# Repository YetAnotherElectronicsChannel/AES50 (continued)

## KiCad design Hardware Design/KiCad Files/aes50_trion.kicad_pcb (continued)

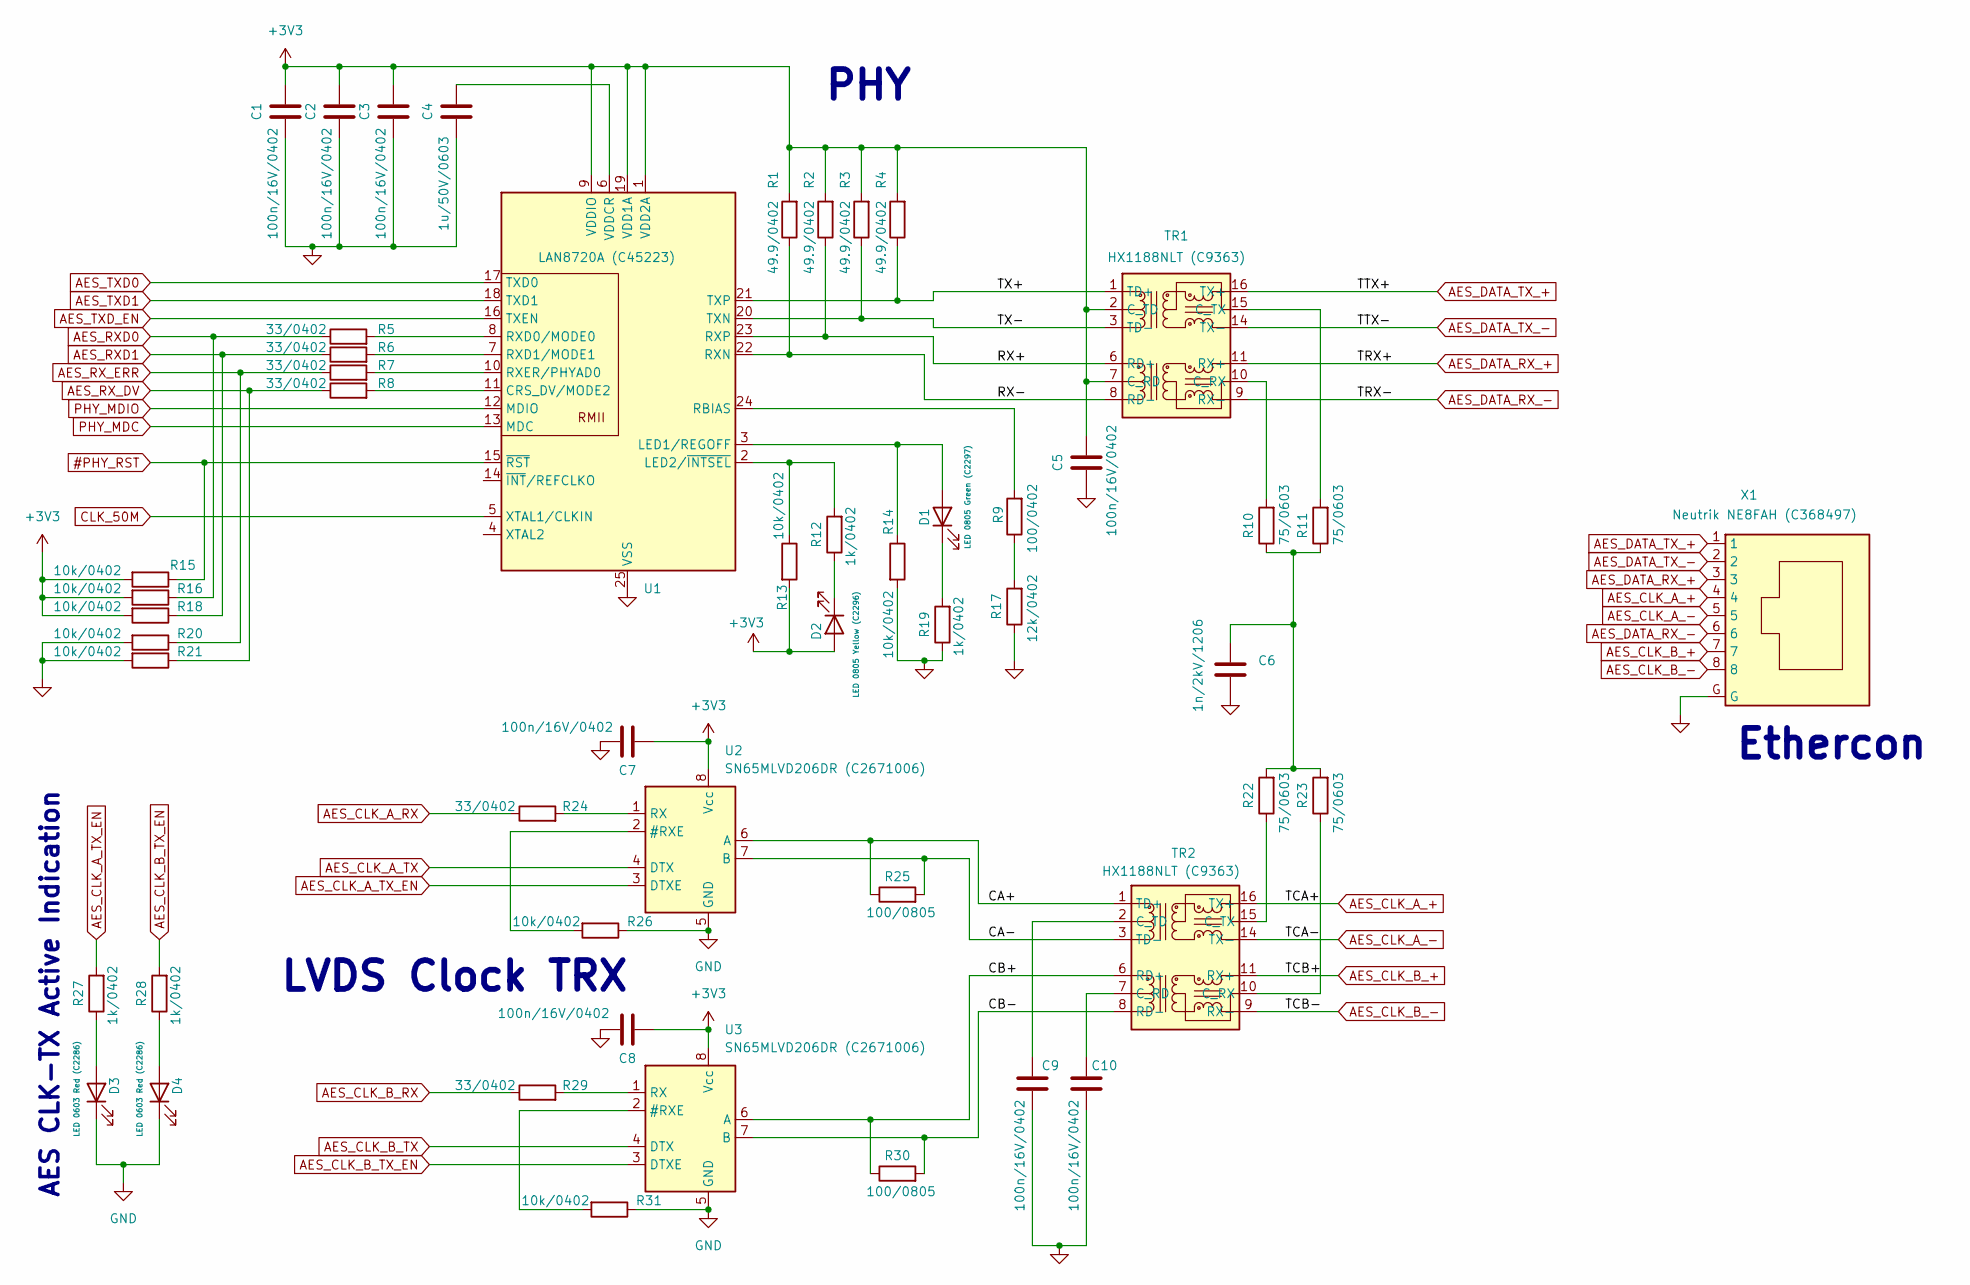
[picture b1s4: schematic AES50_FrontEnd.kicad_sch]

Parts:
C1, C2, C3, C5, C7, C8, C9, C10: 100n/16V/0402; C_0402_1005Metric
C4: 1u/50V/0603; C_0603_1608Metric
C6: 1n/2kV/1206; C_1206_3216Metric
D1: LED 0805 Green (C2297); LED_0805_2012Metric
D2: LED 0805 Yellow (C2296); LED_0805_2012Metric
D3, D4: LED 0603 Red (C2286); LED_0603_1608Metric
R1, R2, R3, R4: 49.9/0402; R_0402_1005Metric
R5, R6, R7, R8, R24, R29: 33/0402; R_0402_1005Metric
R9: 100/0402; R_0402_1005Metric
R10, R11, R22, R23: 75/0603; R_0603_1608Metric
R12, R19, R27, R28: 1k/0402; R_0402_1005Metric
R13, R14, R15, R16, R18, R20, R21, R26, R31: 10k/0402; R_0402_1005Metric
R17: 12k/0402; R_0402_1005Metric
R25, R30: 100/0805; R_0805_2012Metric
TR1, TR2: HX1188NLT (C9363); HX1188NL
U1: LAN8720A (C45223); VQFN-24-1EP_4x4mm_P0.5mm_EP2.5x2.5mm_ThermalVias
U2, U3: SN65MLVD206DR (C2671006); SOIC-8_3.9x4.9mm_P1.27mm
X1: Neutrik NE8FAH (C368497); Neutrik NE8FAH

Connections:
#PHY_RST: R15.1, U1.15 (~RST); also elsewhere on the board
+3V3: C1.2, C2.2, C3.2, C5.2, C7.1, C8.1, D2.2 (A), R1.2, R2.2, R3.2, R4.2, R13.2, R15.2, R16.2, R18.2, TR1.2 (C_TD), TR1.7 (C_RD), U1.1 (VDD2A), U1.9 (VDDIO), U1.19 (VDD1A), U2.8 (Vcc), U3.8 (Vcc); also elsewhere on the board
/AES50_FrontEnd/CA+: R25.1, TR2.1 (TD+), U2.6 (A)
/AES50_FrontEnd/CA-: R25.2, TR2.3 (TD-), U2.7 (B)
/AES50_FrontEnd/CB+: R30.1, TR2.6 (RD+), U3.6 (A)
/AES50_FrontEnd/CB-: R30.2, TR2.8 (RD-), U3.7 (B)
/AES50_FrontEnd/RX+: R2.1, TR1.6 (RD+), U1.23 (RXP)
/AES50_FrontEnd/RX-: R1.1, TR1.8 (RD-), U1.22 (RXN)
/AES50_FrontEnd/TX+: R4.1, TR1.1 (TD+), U1.21 (TXP)
/AES50_FrontEnd/TX-: R3.1, TR1.3 (TD-), U1.20 (TXN)
AES_CLK_A_+: TR2.16 (TX+), X1.4
AES_CLK_A_-: TR2.14 (TX-), X1.5
AES_CLK_A_RX: R24.1; also elsewhere on the board
AES_CLK_A_TX: U2.4 (DTX); also elsewhere on the board
AES_CLK_A_TX_EN: R27.2, U2.3 (DTXE); also elsewhere on the board
AES_CLK_B_+: TR2.11 (RX+), X1.7
AES_CLK_B_-: TR2.9 (RX-), X1.8
AES_CLK_B_RX: R29.1; also elsewhere on the board
AES_CLK_B_TX: U3.4 (DTX); also elsewhere on the board
AES_CLK_B_TX_EN: R28.2, U3.3 (DTXE); also elsewhere on the board
AES_DATA_RX_+: TR1.11 (RX+), X1.3
AES_DATA_RX_-: TR1.9 (RX-), X1.6
AES_DATA_TX_+: TR1.16 (TX+), X1.1
AES_DATA_TX_-: TR1.14 (TX-), X1.2
AES_RXD0: R5.1, R16.1; also elsewhere on the board
AES_RXD1: R6.1, R18.1; also elsewhere on the board
AES_RX_DV: R8.1, R21.1; also elsewhere on the board
AES_RX_ERR: R7.1, R20.1; also elsewhere on the board
AES_TXD0: U1.17 (TXD0); also elsewhere on the board
AES_TXD1: U1.18 (TXD1); also elsewhere on the board
AES_TXD_EN: U1.16 (TXEN); also elsewhere on the board
CLK_50M: U1.5 (XTAL1/CLKIN); also elsewhere on the board
GND: C1.1, C2.1, C3.1, C4.1, C5.1, C6.2, C7.2, C8.2, C9.1, C10.1, D3.1 (K), D4.1 (K), R14.2, R17.1, R19.1, R20.2, R21.2, R26.1, R31.1, U1.25 (VSS), U2.5 (GND), U3.5 (GND), X1.G; also elsewhere on the board
unnamed: C6.1, R10.1, R11.1, R22.2, R23.2
unnamed: D1.2 (A), R14.1, U1.3 (LED1/REGOFF)
unnamed: D1.1 (K), R19.2
unnamed: D2.1 (K), R12.1
unnamed: D3.2 (A), R27.1
unnamed: D4.2 (A), R28.1
unnamed: R9.1, R17.2
unnamed: R10.2, TR1.10 (C_RX)
unnamed: R11.2, TR1.15 (C_TX)
unnamed: C10.2, TR2.7 (C_RD)
unnamed: R23.1, TR2.10 (C_RX)
unnamed: C9.2, TR2.2 (C_TD)
unnamed: R22.1, TR2.15 (C_TX)
unnamed: R8.2, U1.11 (CRS_DV/MODE2)
unnamed: R12.2, R13.1, U1.2 (LED2/~INTSEL)
unnamed: R9.2, U1.24 (RBIAS)
unnamed: R5.2, U1.8 (RXD0/MODE0)
unnamed: R6.2, U1.7 (RXD1/MODE1)
unnamed: R7.2, U1.10 (RXER/PHYAD0)
unnamed: C4.2, U1.6 (VDDCR)
unnamed: R26.2, U2.2 (#RXE)
unnamed: R24.2, U2.1 (RX)
unnamed: R31.2, U3.2 (#RXE)
unnamed: R29.2, U3.1 (RX)
PHY_MDC: U1.13 (MDC); also elsewhere on the board
PHY_MDIO: U1.12 (MDIO); also elsewhere on the board

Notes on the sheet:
AES CLK-TX Active Indication
LVDS Clock TRX
PHY
Ethercon

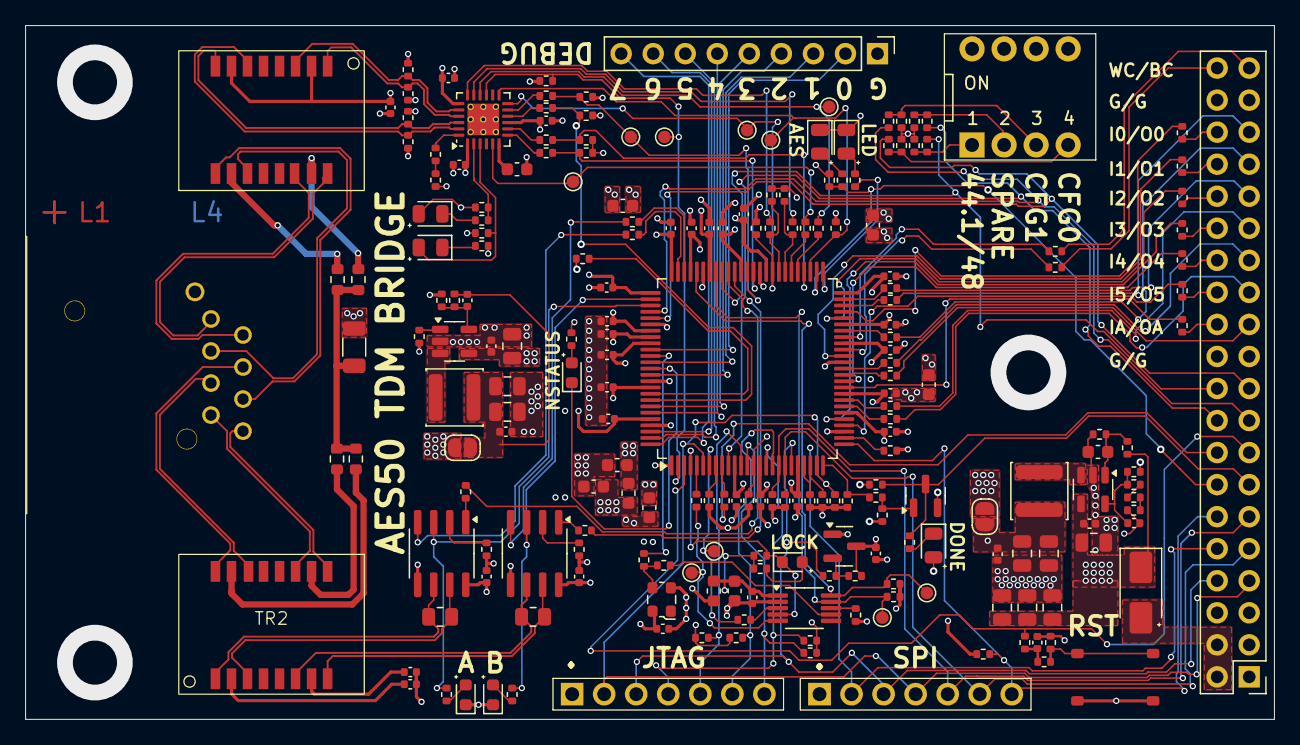
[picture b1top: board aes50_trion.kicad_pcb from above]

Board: 4 copper layers, 99.0 x 55.0 mm, 213 parts (0 on the bottom side), 171 nets.

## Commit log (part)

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2026-03-05 Added AUX-tunnel data-decoder with UART-Output interface. Fixed interface-settings for RMII interface to Phy. Reverted clock-manager to async-reset version
2026-03-26 Fix issue: Bit-Flips in Aux-Decoder
2026-03-26 Fix issue #1 from aspdigital
2026-03-26 Add protocol description pdf
2026-03-27 some additional refactoring...
2026-05-05 Add missing Gerber-Files on request of issue #3
